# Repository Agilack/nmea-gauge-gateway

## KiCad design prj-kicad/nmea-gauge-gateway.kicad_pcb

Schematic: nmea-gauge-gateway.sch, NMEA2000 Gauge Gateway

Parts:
P1: CONN_M12-5
P2: CONN_8; CONN_638263122008
R10, R20: 10k; SMD0805

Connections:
+VIn: P2.8; also elsewhere on the board
+VInP: R10.1, R20.1; also elsewhere on the board
GAUGE1_IN: P2.1; also elsewhere on the board
GAUGE1_OUT: P2.2; also elsewhere on the board
GAUGE1_REF: P2.3, R10.2
GAUGE2_IN: P2.4; also elsewhere on the board
GAUGE2_OUT: P2.5; also elsewhere on the board
GAUGE2_REF: P2.6, R20.2
GND: P2.7; also elsewhere on the board

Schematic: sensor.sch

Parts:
C11, C12, C13, C21, C22, C23: 100nF; SMD0603
D11, D12, D21, D22: TVS; SOD-123
L11, L12, L21, L22: 680nH; SMD0805
Q11, Q21: T_NPN; SOT23-3
R11, R21: 1M; SMD0805
R12, R22: 100k; SMD0805
R15, R25: 1; SMD0805
U11, U12, U21, U22: MCP6001; SC70-5

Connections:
+3.3V: C12.1, C13.1, C22.1, C23.1, U11.5, U12.5, U21.5, U22.5; also elsewhere on the board
GAUGE1: U11.1, U11.4
GAUGE1_IN: L11.1; also elsewhere on the board
GAUGE1_OUT: L12.2; also elsewhere on the board
GAUGE1_VO: U12.3
GAUGE2: U21.1, U21.4
GAUGE2_IN: L21.1; also elsewhere on the board
GAUGE2_OUT: L22.2; also elsewhere on the board
GAUGE2_VO: U22.3
GND: C11.2, C12.2, C13.2, C21.2, C22.2, C23.2, D11.2, D12.2, D21.2, D22.2, R12.1, R15.2, R22.1, R25.2, U11.2, U12.2, U21.2, U22.2; also elsewhere on the board
unnamed: C11.1, R11.1, R12.2, U11.3
unnamed: C21.1, R21.1, R22.2, U21.3
unnamed: D11.1, L11.2, R11.2
unnamed: D12.1, L12.1, Q11.3
unnamed: D21.1, L21.2, R21.2
unnamed: D22.1, L22.1, Q21.3
unnamed: Q11.1, U12.1
unnamed: Q11.2, R15.1, U12.4
unnamed: Q21.1, U22.1
unnamed: Q21.2, R25.1, U22.4

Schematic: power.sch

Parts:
C1, C2, C3: 2,2uF; C_1210
C4: 10nF; SMD0603
C5: 100nF; SMD0603
C6: n/a; SMD0603
C7: 4700pF; SMD0603
C8: C; C_1210
C9: 220uF; C_TPB_D4
D1: TVS; D_SMB
D2: MBRA340; DO214AC
F1: 2920L050DR; SMD_2920
L1: INDUCTOR; I_TYS4012
L2: 27uH; I_MSS1048
R1: 100k; SMD0603
R2: 20k; SMD0603
R3: 47k; SMD0603
R4: 15k; SMD0603
U1: TPS54160A; MSOP10p

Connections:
+3.3V: C8.1, C9.1, L2.2, R3.1; also elsewhere on the board
+VIn: F1.1; also elsewhere on the board
+VInP: C2.1, C3.1, L1.2, U1.2; also elsewhere on the board
/Power Supply/3V3_SW: C5.2, D2.2, L2.1, U1.10
/Power Supply/FUSED_VIN: C1.1, D1.1, F1.2, L1.1
GND: C1.2, C2.2, C3.2, C4.2, C6.2, C7.2, C8.2, C9.2, D1.2, D2.1, R1.2, R4.2, U1.9, U1.PAD; also elsewhere on the board
unnamed: C4.1, U1.4
unnamed: C5.1, U1.1
unnamed: C6.1, R2.1, U1.8
unnamed: C7.1, R2.2
unnamed: R1.1, U1.5
unnamed: R3.2, R4.1, U1.7

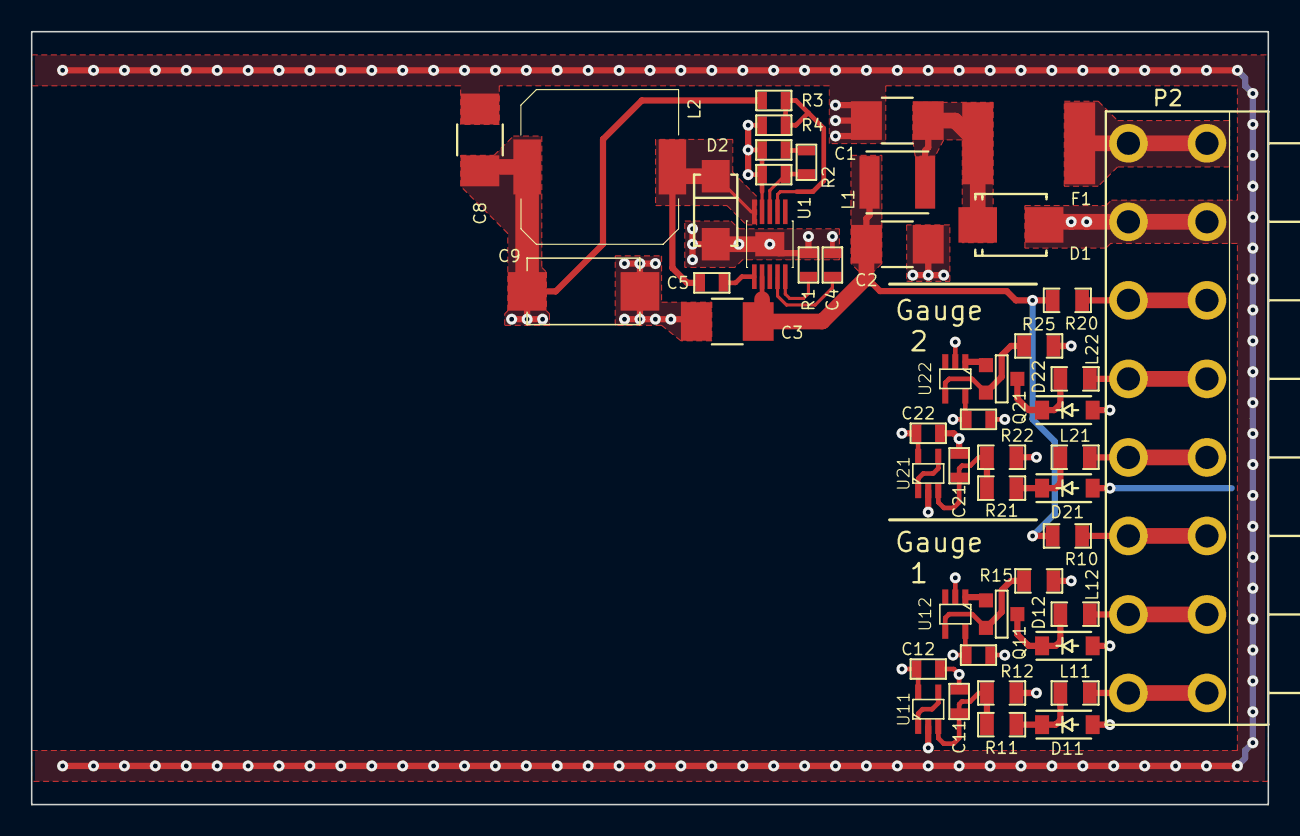
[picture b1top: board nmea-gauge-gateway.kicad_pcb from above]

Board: 4 copper layers, 80.0 x 50.0 mm, 48 parts (0 on the bottom side), 30 nets.

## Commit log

2020-04-04 --=={ Create project }==--
2020-04-07 = ADD: Insert analog inputs/outputs for gauge sensors
2020-04-14 = ADD: Insert power supply
